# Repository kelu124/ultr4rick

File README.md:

# ultr4rick

Ultr4rick is an open ultrasound pulse-echo board, the higher-power successor to
[pic0rick](https://github.com/kelu124/pic0rick). It is built around an **RP2350B** and has:

- a 10-bit, 60 MS/s ADC (AD9215) behind an AD8331 variable-gain front end, with gain set by an MCP4812 DAC;
- a bipolar HV pulser driven by two logic lines (A = negative, B = positive, A+B = damping), fed by a SEPIC HV supply;
- a MAX14866 16-channel HV mux;
- a uSD slot, an LP5562 RGB LED driver on I2C, and USB.

The firmware can compute the Hilbert envelope (and A-law compression) of each 4096-sample capture on the board.

## The board

<table>
  <tr>
    <td width="50%"></td>
    <td width="50%"></td>
  </tr>
  <tr>
    <td><b>Front.</b> HV supply, pulser, RP2350B and receive front end (AFE). <code>PULSER_OUT</code> and
      <code>AFE_IN</code> SMA connectors on the right edge, USB-C and uSD on the left.</td>
    <td><b>Back.</b> The MAX14866 HV mux and the 8 U.FL element connectors (U18–U21, U26–U29).</td>
  </tr>
  <tr>
    <td colspan="2"></td>
  </tr>
  <tr>
    <td colspan="2"><b>Running.</b> Powered over USB-C (about 0.96 W on the inline meter), with one transducer on
      <code>PULSER_OUT</code> and <code>AFE_IN</code> through an SMA tee.</td>
  </tr>
</table>

The KiCad renders are in [`hardware/Ultr4rick_F.png`](hardware/Ultr4rick_F.png) and
[`hardware/Ultr4rick_B.png`](hardware/Ultr4rick_B.png). The photos are described in
[`docs/images/README.md`](docs/images/README.md).

## Acquisition examples

Pulse-echo on the mux: each element in turn on TX and RX with `set_one_mux(k)`, raw ADC trace (top) and on-board
Hilbert envelope (bottom). Elements 2 and 4 show echo trains: about every 13 µs on element 2 and every 20 µs on element 4. From
`python/example_dsp.ipynb`, section 13.

Idle vs. pulsed capture at gain 50, pulse 96/6000/96 ns: the excitation at 0.9 µs, the receiver recovering until
about 6 µs, and the envelope computed on the board. From `python/example_dsp.ipynb`, section 15.

## Repository layout

| Path | Contents |
|---|---|
| `docs/` | Documentation: [start here](docs/README.md) (introduction, setup and first acquisitions, firmware, Python library, repository map) |
| `hardware/` | KiCad project of the v2 board: schematic sheets per subsystem, PCB, gerbers, renders |
| `firmware/` | Pico SDK C firmware for the RP2350B. Pin map in [`firmware/PINMAP.md`](firmware/PINMAP.md), history in [`firmware/CHANGELOG.md`](firmware/CHANGELOG.md) |
| `python/` | `ultr4rick` host library, example script and notebooks. See [`python/Readme.md`](python/Readme.md) |
| `requirements.txt` | Python dependencies for `python/` |
| `TODO.md` | Hardware changes planned for the next revision |
| `LICENSE.md`, `LICENSES/` | Licenses per part of the repository |

## Quick start

Build the firmware (Pico SDK 2.3.0, `arm-none-eabi-gcc`, CMake + Ninja):

```bash
cd firmware
export PICO_SDK_PATH=$HOME/.pico-sdk/sdk/2.3.0
./build.sh -DPICO_TOOLCHAIN_PATH=/usr
# dist/ultr4rick-v<ver>-ultr4rick.uf2      stdio text REPL
# dist/ultr4rick-v<ver>-ultr4rick-dsp.uf2  on-board DSP + binary frames
```

Flashing:

1. Get the board into BOOTSEL. Either send `reboot-dfu` over the serial port, or hold BOOTSEL while plugging it in.
2. Copy the UF2 onto the `RP2350` drive that appears.

Drive it from Python:

```bash
python3 -m venv .venv && .venv/bin/pip install -r requirements.txt
cd python && ../.venv/bin/python example_dsp.py      # status, DSP self-test, captures
../.venv/bin/jupyter lab                            # example_dsp.ipynb, example_acquisition.ipynb, ...
```

```python
from ultr4rick.device import Ultr4rick
from ultr4rick import dsp
probe = Ultr4rick()                  # finds the board by USB ID
print(probe.status()["raw"])
print(dsp.check_selftest(probe.selftest()))
frame = probe.read_fft()             # 4096-sample Hilbert envelope
```

> **Safety:** the pulser generates high voltage. The firmware boots with it disarmed. Only arm it
> (`pulser arm` / `Ultr4rick.arm_pulser()`) with a transducer connected, and disarm it afterwards.

## License

- Hardware (`hardware/`): [TAPR Open Hardware License v1.0](LICENSES/TAPR-OHL-1.0.txt)
- Firmware (`firmware/`) and Python (`python/`): [GPL-3.0-or-later](LICENSES/GPL-3.0-or-later.txt)
- Documentation (`docs/` and the Markdown files): [CC BY-SA 4.0](LICENSES/CC-BY-SA-4.0.txt)

See [`LICENSE.md`](LICENSE.md) for the details and the third-party code.

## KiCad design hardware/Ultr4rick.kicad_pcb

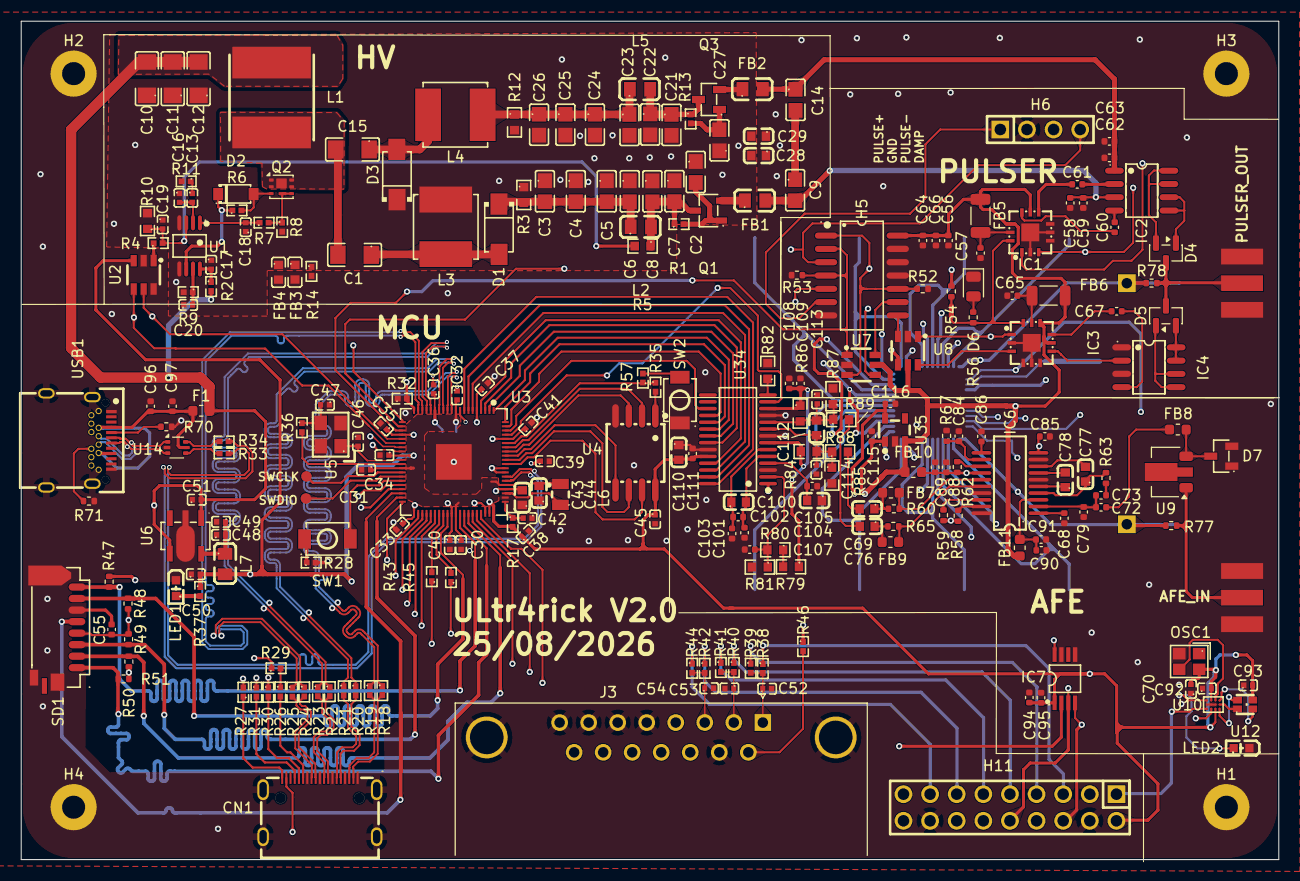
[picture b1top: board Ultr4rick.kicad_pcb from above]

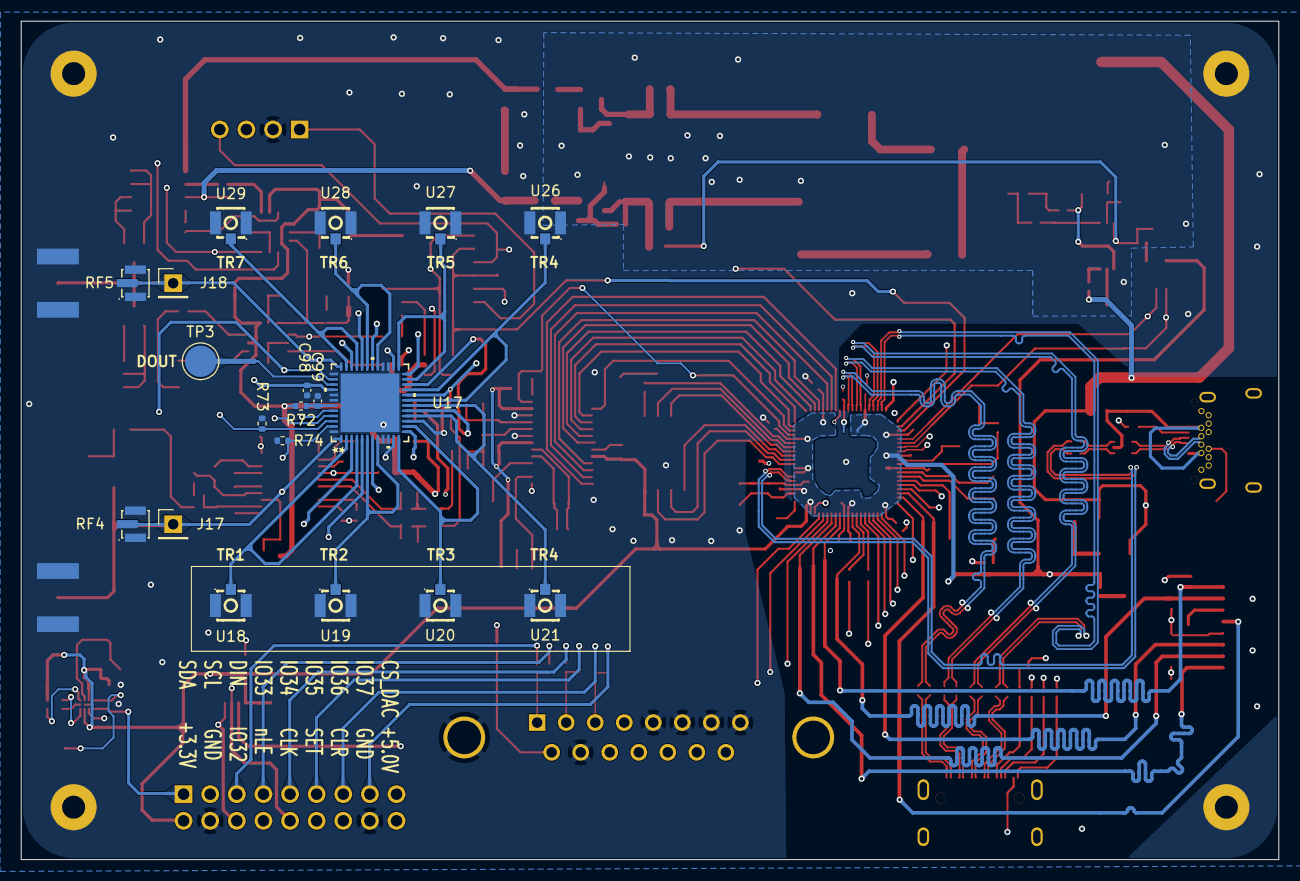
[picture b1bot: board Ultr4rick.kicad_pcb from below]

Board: 4 copper layers, 120.0 x 80.0 mm, 269 parts (19 on the bottom side), 198 nets.

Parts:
C1, C15: 2.2uF; C1206
C2, C3, C4, C5, C6, C7, C8, C21, C22, C23, C24, C25, C26, C27: 2.2uF; C0805
C9, C14: 100nF; C0805
C10, C11: 47uF; C1206
C12: 100nF; C1206
C13, C16, C30, C31, C33, C34, C35, C36, C37, C38, C39, C40, C41, C45, C49: 100nF; C0402
C17, C32, C42, C48: 4.7uF; C0402
C18: 2200pF; C0402
C19, C20: 100pF; C0402
C28, C29: 100nF; C0603
C43, C44: 4.7uF; C0603
C46, C47: 15pF; C0402
C50, C51: 10uF; C0402
C52, C53, C54: 220nF; C0402
C55, C94: 10uF; C_0402_1005Metric
C56, C57, C59, C63, C64, C65, C66, C68, C84, C86, C89, C91, C95, C99, C101, C102, C103, C105, C107, C109, C111: 100nF; C_0402_1005Metric
C58, C62, C98: 1uF; C_0402_1005Metric
C60, C61, C67, C72: 10nF; C_0402_1005Metric
C69, C76, C77, C78: 10nF; C0603
C70: 10nF; C0402
C73: 18nF; C_0402_1005Metric
C79: 22pF; C_0402_1005Metric
C85, C88, C90: 1nF; C_0402_1005Metric
C92, C93: 4u7; C0402
C96, C97: 4u7; C_0402_1005Metric
C100, C104, C110: 10uF; C0603
C108, C115, C116: 4.7uF; C_0402_1005Metric
C112: 100pF; C0603
C113, C114: 22pF; C0402
CN1: A71-05H4-111N1; HDMI-SMD_A71-05H4-111N1
D1, D3: SS320_C18199172; SMA_L4.3-W2.6-LS5.0-RD
D2: 1N4148W T4; SOD-123_L2.8-W1.8-LS3.7-RD
D4, D5: BAV99; SOT-23
D6: Green LED; D_0805_2012Metric
D7: BAV99-7-F; SOT-23-3_L2.9-W1.3-P1.90-LS2.4-BR
F1: 1A; Fuse_0603_1608Metric
FB1, FB2: 1.2Ω; L0805
FB3, FB4: 8.5Ω; L0603
FB5, FB6: 120Ohm 3 A; L_1206_3216Metric
FB7, FB8, FB9, FB10, FB11: L_0603_1608Metric
H1, H2, H3, H4: MountingHole_Pad; MountingHole_2.2mm_M2_Pad
H5: TC74VHC08F_EL,K,F_; SOP-14_L10.2-W5.3-P1.27-LS7.8-BL
H6: Header-Male-2.54_1x4; HDR-TH_4P-P2.54-V-M
H11: HX PZ2.54-2X9P ZZ; HDR-TH_18P-P2.54-V-M-R2-C9-S2.54-1
IC1, IC3: MD1213K6-G; QFN-12_L4.0-W4.0-P0.80-BL-EP1.7
IC2, IC4: TC6320TG-G; SOIC-8_L4.9-W3.9-P1.27-LS6.0-BL
IC6: AD8331ARQZ; QSOP-20_L8.7-W3.9-P0.64-LS6.0-BL
IC7: MCP4812-E_MS; MSOP-8_L3.0-W3.0-P0.65-LS4.9-BL
J1, J2: SMA_Edge; SMA_Edge_8mm
J3: DE15_Socket_HighDensity_MountingHoles; DSUB-15_Socket_Horizontal_P2.77x2.84mm_EdgePinOffset9.90mm_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
J17, J18: Conn_01x01_Pin; PinHeader_1x01_P2.54mm_Vertical
L1: 100uH; IND-SMD_L8.0-W8.0
L2, L5: 10uH; L0805
L3, L4: 1mH; IND-SMD_L6.0-W6.0_SWPA6045S
L6: 3.3uH; IND-SMD_L2.0-W1.6_AOTA-B201610S3R3-101-T
L7: MH2029-601Y; L0805
LED1, LED2: KT-0603R; LED-SMD_L1.6-W0.8-R-RD
NT1: NetTie_2; NetTie-2_SMD_Pad0.5mm
OSC1: SX2M32.768KM20F30TNN; OSC-SMD_4P-L2.5-W2.0-BL
Q1: FMMT495TA; SOT-23-3_L2.9-W1.6-P1.90-LS2.8-BR
Q2: CSD19538Q2; Texas_DQK
Q3: FMMT596TA; SOT-23-3_L2.9-W1.3-P1.90-LS2.4-BR
R1, R13: 10k; R0402
R2, R33, R34: 22Ω; R0402
R3, R12: 100k; R0603
R4: 56k; R0402
R5: 330k; R0603
R6: 1Ω; R0402
R7, R43, R45, R46: 100Ω; R0402
R8: 0.1Ω; R0402
R9: 40.2k; R0402
R10: 5.1k; R0603
R11: 4.7k; R0402
R14, R35: 0Ω; R0402
R17: 33Ω; R0402
R18, R19, R20, R21, R22, R23, R24, R25, R26: 200Ω; R0402
R27: 1.8kΩ; R0402
R28, R36, R57: 1kΩ; R0402
R29, R30, R31: 2.2kΩ; R0402
R32: 3.3kΩ; R0402
R37: 330Ω; R0402
R38, R40, R42: 510Ω; R0402
R39, R41, R44: 1KΩ; R0402
R47, R48, R49, R50, R51, R52, R53, R54, R58, R59, R62, R73, R74: 10K; R_0402_1005Metric
R56: 1K; R_0402_1005Metric
R60, R65: 100R; R_0402_1005Metric
R63: 280R; R_0402_1005Metric
R67: 12K; R_0402_1005Metric
R70, R71: 5K1; R_0402_1005Metric
R72: 10R; R_0402_1005Metric
R77, R78: 0Ω; R_0402_1005Metric
R79, R80, R81, R82, R84, R85, R86, R87: 1k; R0603
R88, R89: 18R; R0603
RF4, RF5: CONUFL001-SMD-T; IPEX-SMD_3P-L2.6-W2.6-LS3.0
SD1: TF-027-H300; TF-SMD_HYCW104-TF08-375B
SW1, SW2: TS-1088-AR02016; SW-SMD_L3.9-W3.0-P4.45
TP1, TP2: 1.0mm; TestPoint-1.0mm
TP3: TestPoint; TestPoint_Pad_D3.0mm
U1: LM3488MMX/NOPB; VSSOP-8_L3.0-W3.0-P0.65-LS4.9-BL
U2: MCP4725A1T-E/CH; SOT-23-6_L2.9-W1.6-P0.95-LS2.8-BR
U3: RP2350B; QFN-80_L10.0-W10.0-P0.40-TL-EP3.4
U4: W25Q128JVSIM; SOIC-8_L5.2-W5.2-P1.27-LS7.9-BL
U5: 12MHz; OSC-SMD_4P-L3.2-W2.5-BL_SIT8008BI
U6: XC6220B331PR-G; SOT-89-5_L4.5-W2.5-P1.50-LS4.4-BR
U7, U8: SN74LVC2G04DBVT; SOT-23-6_L2.9-W1.6-P0.95-LS2.8-BR
U9: MD0100N8-G; SOT-89-3
U10: LP5562TMX/NOPB; DSBGA-12_L1.7-W1.3-R3-C4-P0.40-TL
U12: A-SP1943B1GHR6C-C01-2T; LED-SMD_4P-L1.6-W1.5-BL_A-SP1943B1GHR6C-C01-2T
U14: USBLC6-2P6; SOT-666
U17: MAX14866UTM+T; 21-0144H_T4877-6_MXM
U18, U19, U20, U21, U26, U27, U28, U29: BWU.FL-IPEX1; IPEX-SMD_BWIPX-1-001E
U34: AD9215BRUZRL7-65; TSSOP-28_L9.7-W4.4-P0.65-LS6.4-BL
U35: XC6210B302MR; SOT-23-5_L2.9-W1.6-P0.95-LS2.8-BR
USB1: TYPEC-503DSL-ACP24; USB-C-SMD_TYPEC-324-BCP24

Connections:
5VLNA: C90.1, C91.1, FB11.2, IC6.3 (VPSL)
5VVGA: C88.1, C89.1, FB10.1, IC6.14 (VPOS), R58.1, R59.1, R62.1
+1.1V: C30.1, C31.1, C32.2, C44.2, L6.2, U3.10 (DVDD), U3.32 (DVDD), U3.51 (DVDD), U3.65 (VREG_FB)
+3.3V: C33.1, C34.1, C35.1, C36.1, C37.1, C38.1, C39.1, C40.1, C41.1, C43.2, C45.1, C50.2, C55.2, C70.2, C92.2, C93.2, C94.1, C95.1, C98.2, C110.2, C111.1, H11.2, IC7.1 (VDD), L7.2, OSC1.4 (VDD), R17.2, R37.1, R47.1, R48.1, R49.1, R50.1, R51.1, R54.1, SD1.4 (VDD), U2.3 (VDD), U3.5 (IOVDD), U3.15 (IOVDD), U3.24 (IOVDD), U3.29 (IOVDD), U3.41 (IOVDD), U3.50 (IOVDD), U3.59 (ADC_AVDD), U3.60 (IOVDD), U3.64 (VREG_VIN), U3.68 (USB_OTP_VDD), U3.69 (QSPI_IOVDD), U3.76 (IOVDD), U4.8 (VCC), U10.A2 (VDD), U10.C3 (EN/VCC), U12.3, U17.40 (VDD), U34.24 (DRVDD)
+5V: C10.2, C11.2, C12.2, C51.2, C56.1, C64.1, C66.1, C115.1, CN1.18 (+5V), F1.2, FB5.1, FB6.1, FB10.2, FB11.1, H5.14 (VCC), H11.18, IC1.8 (VH), IC1.10 (VDD2), IC3.8 (VH), IC3.10 (VDD2), L1.1 (+), R2.2, R46.1, R72.2, U6.1 (CE), U6.4 (VIN), U7.5 (VCC), U8.5 (VCC), U35.1 (VIN), U35.3 (CE)
+HV: C9.2, C58.2, C59.2, FB1.2, IC2.3 (SP)
-HV: C14.1, C62.2, C63.2, FB2.2, IC2.1 (SN)
/DAC+AFE/ECHO_IN: J2.1 (In), R77.2, U9.1 (A)
/MUX/DOUT: TP3.1 (1_1), U17.39 (DOUT)
/MUX/MUX_IN: J17.1 (Pin_1_1), R77.1, RF4.1, U17.1 (COM0), U17.5 (COM2), U17.11 (COM4), U17.15 (COM6), U17.20 (COM8), U17.24 (COM10), U17.30 (COM12), U17.34 (COM14)
/MUX/MUX_OUT: J18.1 (Pin_1_1), R78.1, RF5.1, U17.3 (COM1), U17.7 (COM3), U17.13 (COM5), U17.17 (COM7), U17.22 (COM9), U17.26 (COM11), U17.32 (COM13), U17.36 (COM15)
/MUX/NO0: U17.2 (NO0), U17.4 (NO1), U18.1
/MUX/NO2: U17.6 (NO2), U17.8 (NO3), U19.1
/MUX/NO4: U17.12 (NO4), U17.14 (NO5), U20.1
/MUX/NO6: U17.16 (NO6), U17.18 (NO7), U21.1
/MUX/NO8: U17.19 (NO8), U17.21 (NO9), U26.1
/MUX/NO10: U17.23 (NO10), U17.25 (NO11), U27.1
/MUX/NO12: U17.29 (NO12), U17.31 (NO13), U28.1
/MUX/NO14: U17.33 (NO14), U17.35 (NO15), U29.1
/MUX/TX: D4.3 (K), D5.3 (K), J1.1 (In), R78.2
/RP2350B/BLUE: C54.1, J3.3, R42.2, R44.2
/RP2350B/BOOT: SW1.1, U3.35 (RUN)
/RP2350B/GREEN: C53.1, J3.2, R40.2, R41.2
/RP2350B/HDMI_CLK_N: CN1.12 (TMDS_CLOCK-), R25.2
/RP2350B/HDMI_CLK_P: CN1.11 (TMDS_CLOCK+), R24.2
/RP2350B/HDMI_D0_N: CN1.9 (TMDS_DATA0-), R23.2
/RP2350B/HDMI_D0_P: CN1.8 (TMDS_DATA0+), R22.2
/RP2350B/HDMI_D1_N: CN1.6 (TMDS_DATA1-), R21.2
/RP2350B/HDMI_D1_P: CN1.5 (TMDS_DATA1+), R20.2
/RP2350B/HDMI_D2_N: CN1.3 (TMDS_DATA2-), R19.2
/RP2350B/HDMI_D2_P: CN1.2 (TMDS_DATA2+), R18.2
/RP2350B/RED: C52.1, J3.1, R38.2, R39.2
/RP2350B/SWCLK: TP1.1 (1_1), U3.33 (SWCLK)
/RP2350B/SWDIO: TP2.1 (1_1), U3.34 (SWDIO)
/RP2350B/USB_DN: R33.1, U3.66 (USB_DM)
/RP2350B/USB_DP: R34.1, U3.67 (USB_DP)
/SEPIC_HV/Vfb: C19.2, R4.2, R5.2, R10.1, U1.3 (FB)
/USB3/USB_DDN: R33.2, U14.4 (IO2)
/USB3/USB_DDP: R34.2, U14.6 (IO1)
/USB3/VBUS: C96.2, C97.1, F1.1, U14.5 (VBUS), USB1.A4 (VBUS), USB1.A9 (VBUS), USB1.B4 (VBUS), USB1.B9 (VBUS)
ADC_0: U3.78 (GPIO1), U34.17 (D0(LSB))
ADC_1: U3.79 (GPIO2), U34.18 (D1)
ADC_2: U3.80 (GPIO3), U34.19 (D2)
ADC_3: U3.1 (GPIO4), U34.20 (D3)
ADC_4: U3.2 (GPIO5), U34.21 (D4)
ADC_5: U3.3 (GPIO6), U34.22 (D5)
ADC_6: U3.4 (GPIO7), U34.25 (D6)
ADC_7: U3.6 (GPIO8), U34.26 (D7)
ADC_8: U3.7 (GPIO9), U34.27 (D8)
ADC_9: U3.8 (GPIO10), U34.28 (D9(MSB))
ADC_CLK: U3.77 (GPIO0), U34.13 (CLK)
AVDD: C108.1, C109.1, C116.1, R79.1, R84.1, R86.1, U34.7 (AVDD), U34.12 (AVDD), U35.5 (OUT)
AVSS: C9.1, C14.2
B: U10.A4 (B), U12.4
CLK: H11.10, IC7.3 (SCK), U3.27 (GPIO26), U17.45 (CLK)
CLK_N: R25.1, U3.19 (GPIO19)
CLK_P: R24.1, U3.18 (GPIO18)
CLR: H11.14, R74.1, U3.37 (GPIO29), U17.47 (CLR)
CS_DAC: H11.17, IC7.2 (~CS), U3.9 (GPIO11)
DAC_G: C85.1, IC6.10 (GAIN), IC7.8 (VOUTA)
DAMP: H5.3 (1Y), H6.4, IC3.1 (INA), U8.1 (1A)
DIN: H11.6, IC7.4 (SDI), U3.28 (GPIO27), U17.44 (DIN)
DVI_CEC: R29.1, U3.57 (GPIO46_ADC6)
DVI_D0_N: R23.1, U3.17 (GPIO17)
DVI_D0_P: R22.1, U3.16 (GPIO16)
DVI_D1_N: R21.1, U3.14 (GPIO15)
DVI_D1_P: R20.1, U3.13 (GPIO14)
DVI_D2_N: R19.1, U3.12 (GPIO13)
DVI_D2_P: R18.1, U3.11 (GPIO12)
DVI_SCL: R30.1, U3.56 (GPIO45_ADC5)
DVI_SDA: R31.1, U3.55 (GPIO44_ADC4)
G: U10.B4 (G), U12.1
GND: C28.1, C29.1, C30.2, C31.2, C32.1, C33.2, C34.2, C35.2, C36.2, C37.2, C38.2, C39.2, C40.2, C41.2, C42.1, C43.1, C44.1, C45.2, C46.1, C47.1, C48.1, C49.2, C50.1, C51.1, C52.2, C53.2, C54.2, C55.1, C56.2, C57.1, C58.1, C59.1, C62.1, C63.1, C64.2, C65.1, C66.2, C68.1, C70.1, C79.2, C84.2, C85.2, C86.2, C88.2, C89.2, C90.2, C91.2, C92.1, C93.1, C94.2, C95.2, C96.1, C97.2, C98.1, C99.1, C101.1, C103.1, C104.1, C105.2, C107.2, C108.2, C109.2, C110.1, C111.2, C113.1, C114.2, C115.2, C116.2, CN1.1 (TMDS_DATA2_SHIELD), CN1.4 (TMDS_DATA1_SHIELD), CN1.7 (TMDS_DATA0_SHIELD), CN1.10 (TMDS_CLOCK_SHIELD), CN1.13 (DDC/CEC_GND), CN1.20 (SHELL), CN1.21 (SHELL), CN1.22 (SHELL), CN1.23 (SHELL), D6.1, D7.1, D7.2, FB3.2, FB4.2, H1.1 (1_1), H2.1 (1_1), H3.1 (1_1), H4.1 (1_1), H5.7 (GND), H5.11 (4Y), H5.12 (4A), H5.13 (4B), H6.2, H11.4, H11.16, IC1.2 (VL), IC1.4 (GND_1), IC1.5 (VSS1), IC1.6 (VSS2), IC1.13 (GND_2), IC3.2 (VL), IC3.4 (GND_1), IC3.5 (VSS1), IC3.6 (VSS2), IC3.13 (GND_2), IC4.1 (SN), IC4.3 (SP), IC6.6 (COML), IC6.9 (MODE), IC6.17 (COMM_1), IC6.20 (COMM_2), IC7.5 (~LDAC), IC7.7 (VSS), J1.2 (Ext), J2.2 (Ext), J3.5, J3.6, J3.7, J3.8, J3.10, J3.SH, LED1.2 (K), LED2.2 (K), OSC1.2 (GND), R14.2, R28.2, R32.1, R52.2, R53.2, R67.2, R70.1, R71.2, R73.2, R74.2, R81.2, R82.2, R85.2, R87.2, RF4.2, RF4.3, RF5.2, RF5.3, SD1.6 (VSS), SD1.10, SD1.11, SW2.2, U2.2 (VSS), U2.6 (A0), U3.62 (VREG_PGND), U3.81 (GND), U4.4 (GND), U5.2 (GND), U5.4 (GND), U6.2 (VSS), U7.2 (GND), U8.2 (GND), U10.B1 (ADDR_SEL1), U10.B2 (ADDR_SEL0), U10.B3 (GND), U14.2 (GND), U17.9 (GND), U17.10 (GND), U17.27 (GND), U17.28 (GND), U17.37 (GND), U17.41 (GND), U17.42 (GND), U17.48 (GND), U17.49 (EPAD), U18.2, U18.3, U19.2, U19.3, U20.2, U20.3, U21.2, U21.3, U26.2, U26.3, U27.2, U27.3, U28.2, U28.3, U29.2, U29.3, U34.3 (SENSE), U34.8 (AGND), U34.11 (AGND), U34.23 (DRGND), U35.2 (GND), USB1.1 (EH), USB1.2 (EH), USB1.3 (EH), USB1.4 (EH), USB1.A1 (GND), USB1.A12 (GND), USB1.B1 (GND), USB1.B12 (GND)
GPIO20: R27.2, R32.2, U3.20 (GPIO20)
GPIO32: H11.5, R38.1, U3.40 (GPIO32)
GPIO33: H11.7, R39.1, U3.42 (GPIO33)
GPIO34: H11.9, R40.1, U3.43 (GPIO34)
GPIO35: H11.11, R41.1, U3.44 (GPIO35)
GPIO36: H11.13, R42.1, U3.45 (GPIO36)
GPIO37: H11.15, R44.1, U3.46 (GPIO37)
GPIO38: R43.2, U3.47 (GPIO38)
GPIO39: R45.2, U3.48 (GPIO39)
HVGND: C2.1, C3.1, C4.1, C5.1, C6.1, C7.1, C8.1, C10.1, C11.1, C12.1, C16.1, C17.1, C18.1, C19.1, C20.1, C21.2, C22.2, C23.2, C24.2, C25.2, C26.2, C27.1, C28.2, C29.2, D3.1 (K), FB3.1, FB4.1, L3.1 (+), R3.1, R8.2, R9.2, R10.2, R11.2, R12.2, R14.1, U1.4 (AGND), U1.5 (PGND)
I2C0_SCL: H11.3, U2.4 (SDA), U3.26 (GPIO25), U10.C2 (SCL)
I2C0_SDA: H11.1, U2.5 (SCL), U3.25 (GPIO24), U10.C1 (SDA)
INPUT_A: H5.1 (1A), H5.10 (3B), R52.1, U3.22 (GPIO22), U7.3 (2A)
INPUT_B: H5.2 (1B), H5.4 (2A), R53.1, U3.23 (GPIO23), U7.1 (1A)
unnamed: C13.1, R11.1
unnamed: C47.2, R36.1, U5.3
unnamed: C69.1, FB7.2, R60.2
unnamed: C72.1, FB8.2
unnamed: C73.2, R63.1
unnamed: C76.1, FB9.2, R65.2
unnamed: CN1.14 (CEC), R26.2
unnamed: CN1.19 (HP_DETECT), R27.1
unnamed: CN1.15 (SCL), R30.2
unnamed: CN1.16 (SDA), R31.2
unnamed: C1.1, D1.2 (A), L3.2 (-)
unnamed: C3.2, C4.2, C5.2, C6.2, D1.1 (K), L2.1 (+), R3.2
unnamed: D2.2 (A), Q2.3 (G), R6.2
unnamed: D2.1 (K), R6.1, U1.6 (DR)
unnamed: C15.1, D3.2 (A), L4.2 (-)
unnamed: D4.2 (A), IC2.7 (DN_1), IC2.8 (DN_2)
unnamed: D5.2 (A), IC4.7 (DN_1), IC4.8 (DN_2)
unnamed: D6.2, R56.2
unnamed: H5.5 (2B), U7.4 (2Y)
unnamed: H5.9 (3A), U7.6 (1Y)
unnamed: H5.8 (3Y), U8.3 (2A)
unnamed: C60.1, IC1.9 (OUTA)
unnamed: C61.1, IC1.7 (OUTB)
unnamed: C57.2, FB5.2, IC1.11 (VDD1)
unnamed: D4.1 (K), IC2.5 (DP_1), IC2.6 (DP_2)
unnamed: C61.2, IC2.2 (GN)
unnamed: C60.2, IC2.4 (GP)
unnamed: C67.1, IC3.9 (OUTA)
unnamed: IC3.7 (OUTB), IC4.2 (GN)
unnamed: C65.2, FB6.2, IC3.11 (VDD1)
unnamed: D5.1 (K), IC4.5 (DP_1), IC4.6 (DP_2)
unnamed: C67.2, IC4.4 (GP)
unnamed: IC6.19 (ENBL), R58.2
unnamed: IC6.18 (ENBV), R59.2
unnamed: IC6.13 (HILO), R62.2
unnamed: C72.2, C73.1, C79.1, IC6.2 (INH)
unnamed: C68.2, IC6.1 (LMD)
unnamed: C77.1, IC6.4 (LON), R63.2
unnamed: C78.1, IC6.5 (LOP)
unnamed: C84.1, IC6.12 (RCLMP), R67.1
unnamed: C86.1, IC6.11 (VCM)
unnamed: C77.2, IC6.8 (VIN)
unnamed: C78.2, IC6.7 (VIP)
unnamed: J3.9, R46.2
unnamed: J3.13, R43.1
unnamed: J3.14, R45.1
unnamed: C1.2, C15.2, L1.2 (-), Q2.1 (D), Q2.2 (D), Q2.5 (D), Q2.6 (D), Q2.8 (D)
unnamed: C7.2, C8.2, L2.2 (-), Q1.3 (C), R1.1, R5.1
unnamed: C23.1, C24.1, C25.1, C26.1, L4.1 (+), L5.1 (+), R12.1
unnamed: C21.1, C22.1, L5.2 (-), Q3.3 (C), R13.1
unnamed: LED1.1 (A), R37.2
unnamed: LED2.1 (A), U10.A1 (W)
unnamed: OSC1.3 (OUTPUT), U10.A3 (CLK_32K)
unnamed: C2.2, Q1.1 (B), R1.2
unnamed: FB1.1, Q1.2 (E)
unnamed: Q2.4 (S), Q2.7 (S), R7.2, R8.1
unnamed: C27.2, Q3.1 (B), R13.2
unnamed: FB2.1, Q3.2 (E)
unnamed: R26.1, R29.2
unnamed: R28.1, SW1.2
unnamed: R57.2, SW2.1
unnamed: R79.2, R80.1
unnamed: C13.2, C16.2, U1.2 (COMP)
unnamed: C20.2, R9.1, U1.7 (FA)
unnamed: C18.2, R7.1, U1.1 (ISEN)
unnamed: C17.2, R2.1, U1.8 (VIN)
unnamed: C42.2, R17.1, U3.61 (VREG_AVDD)
unnamed: L6.1, U3.63 (VREG_LX)
unnamed: R35.2, U4.1 (/CS)
unnamed: C48.2, C49.1, L7.1, U6.5 (VOUT)
unnamed: D7.3, FB8.1, U9.3 (B)
unnamed: C99.2, R72.1, U17.43 (VCC)
unnamed: C107.1, R80.2, R81.1, U34.2 (MODE)
unnamed: R82.1, U34.14 (PDWN)
unnamed: C100.2, C101.2, C102.1, U34.5 (REFB)
unnamed: C100.1, C102.2, C103.2, U34.6 (REFT)
unnamed: C112.1, C114.1, R84.2, R85.1, R88.1, U34.9 (VIN+)
unnamed: C112.2, C113.2, R86.2, R87.1, R89.1, U34.10 (VIN–)
unnamed: C104.2, C105.1, U34.4 (VREF)
unnamed: R70.2, USB1.A5 (CC1)
unnamed: R71.1, USB1.B5 (CC2)
OE: IC1.12 (OE), IC3.12 (OE), NT1.2, R56.1
OE_HV: NT1.1, R54.2
OR: U3.58 (GPIO47_ADC7), U34.1 (OR)
PULSE+: H5.6 (2Y), H6.1, IC1.1 (INA)
PULSE-: H6.3, IC1.3 (INB), U8.4 (2Y)
QSPI_SCLK: U3.71 (QSPI_SCLK), U4.6 (CLK)
QSPI_SD0: U3.72 (QSPI_SD0), U4.5 (DI(IO0))
QSPI_SD1: U3.74 (QSPI_SD1), U4.2 (DO(IO1))
QSPI_SD2: U3.73 (QSPI_SD2), U4.3 (/WP(IO2))
QSPI_SD3: U3.70 (QSPI_SD3), U4.7 (/HOLDor/RESET(IO3))
QSPI_SS: R35.1, R57.1, U3.75 (QSPI_SS)
R: U10.C4 (R), U12.2
SD_CMD: R49.2, SD1.3 (CMD), U3.39 (GPIO31)
SD_D0: R48.2, SD1.7 (DAT0), U3.49 (GPIO40_ADC0)
SD_D1: R47.2, SD1.8 (DAT1), U3.52 (GPIO41_ADC1)
SD_D2: R51.2, SD1.1 (DAT2), U3.53 (GPIO42_ADC2)
SD_D3: R50.2, SD1.2 (CD/DAT3), U3.54 (GPIO43_ADC3)
SD_SCK: SD1.5 (CLK), U3.38 (GPIO30)
SET: H11.12, R73.1, U3.36 (GPIO28), U17.46 (SET)
TO_ADC_H: C69.2, R88.2
TO_ADC_L: C76.2, R89.2
UD+: U14.1 (IO1), USB1.A6 (DP1), USB1.B6 (DP2)
UD-: U14.3 (IO2), USB1.A7 (DN1), USB1.B7 (DN2)
VOH: FB7.1, IC6.15 (VOH), R60.1
VOL: FB9.1, IC6.16 (VOL), R65.1
Vadj: R4.1, U2.1 (VOUT)
XIN: C46.2, U3.30 (XIN), U5.1
XOUT: R36.2, U3.31 (XOUT)
nLE: H11.8, U3.21 (GPIO21), U17.38 (*LE)
~DAMP: IC3.3 (INB), U8.6 (1Y)

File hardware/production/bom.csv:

Designator,Footprint,Quantity,Value,LCSC Part #
"C1, C15",C1206,2,2.2uF,C170101
"C10, C11",C1206,2,47uF,C403725
"C100, C104, C110",C0603,3,10uF,C96446
"C101, C102, C103, C105, C107, C109, C111, C68, C84, C86, C89, C91, C95",0402,13,100nF,C1525 
"C108, C115, C116",0402,3,4.7uF,C318563 
C112,C0603,1,100pF,C14858
"C113, C114",C0402,2,22pF,C1555
C12,C1206,1,100nF, C1945
"C13, C16",C0402,2,100nF,C162178
"C14, C9",C0805,2,100nF,C28233
C17,C0402,1,4.7uF,C6119795
C18,C0402,1,2200pF,C710671
"C19, C20",C0402,2,100pF,C576700
"C2, C21, C22, C26, C27, C6, C7, C8",C0805,8,2.2uF, C22367838
"C23, C24, C25, C3, C4, C5",C0805,6,2.2uF,C22367838
"C28, C29",C0603,2,100nF,C77058
"C30, C31, C33, C34, C35, C36, C37, C38, C39, C40, C41, C45, C49",C0402,13,100nF,C152814
"C32, C42, C48",C0402,3,4.7uF,C5718966
"C43, C44",C0603,2,4.7uF,C5360844
"C46, C47",C0402,2,15pF,C326803
"C50, C51",C0402,2,10uF,C315248
"C52, C53, C54",C0402,3,220nF,C71693
"C55, C94",0402,2,10uF,C315248 
"C56, C57, C59, C63, C64, C65, C66",0402,7,100nF,C1525
"C58, C62",0402,2,1uF,C52923
"C60, C61, C67",0402,3,10nF,C15195
"C69, C76",C0603,2,10nF,C76599
C70,C0402,1,10nF,C15195
C72,0402,1,10nF,C1518210
C73,0402,1,18nF,C106202 
"C77, C78",C0603,2,10nF,C85973
C79,0402,1,22pF,C1864677 
"C85, C88, C90",0402,3,1nF,C77018 
"C92, C93",C0402,2,4u7,C326586
"C96, C97",0402,2,4u7,C326586
C98,0402,1,1uF,C1525  
C99,0402,1,100nF,C1525  
CN1,HDMI-SMD_A71-05H4-111N1,1,A71-05H4-111N1,C2682170
"D1, D3",SMA_L4.3-W2.6-LS5.0-RD,2,SS320_C18199172,C18199172
D2,SOD-123_L2.8-W1.8-LS3.7-RD,1,1N4148W T4,C2099
"D4, D5",SOT-23,2,BAV99,C2500
D6,0805,1,Green LED,C84260
D7,SOT-23-3_L2.9-W1.3-P1.90-LS2.4-BR,1,BAV99-7-F,C106919 
F1,0603,1,1A,C207017
"FB1, FB2",L0805,2,1.2Ω,C46435
"FB10, FB11, FB7, FB8, FB9",0603,5,~,C14709 
"FB3, FB4",L0603,2,8.5Ω,C5339211
"FB5, FB6",1206,2,120Ohm 3 A,C98293
H11,HDR-TH_18P-P2.54-V-M-R2-C9-S2.54-1,1,HX PZ2.54-2X9P ZZ,C42372517
H5,SOP-14_L10.2-W5.3-P1.27-LS7.8-BL,1,"TC74VHC08F_EL,K,F_",C6880155
H6,HDR-TH_4P-P2.54-V-M,1,Header-Male-2.54_1x4,C124378
"IC1, IC3",QFN-12_L4.0-W4.0-P0.80-BL-EP1.7,2,MD1213K6-G,C621434
"IC2, IC4",SOIC-8_L4.9-W3.9-P1.27-LS6.0-BL,2,TC6320TG-G,C624992
IC6,QSOP-20_L8.7-W3.9-P0.64-LS6.0-BL,1,AD8331ARQZ,C578697 
IC7,MSOP-8_L3.0-W3.0-P0.65-LS4.9-BL,1,MCP4812-E_MS,C219484 
"J1, J2",SMA_Edge_8mm,2,SMA_Edge,RFPC-SMA23-FN-095-A
"J17, J18",PinHeader_1x01_P2.54mm_Vertical,2,Conn_01x01_Pin,C81276 
J3,DSUB-15_Socket_Horizontal_P2.77x2.84mm_EdgePinOffset9.90mm_Housed_MountingHolesOffset11.32mm,1,DE15_Socket_HighDensity_MountingHoles,C3108041
L1,IND-SMD_L8.0-W8.0,1,100uH,C142103
"L2, L5",L0805,2,10uH,C52723027
"L3, L4",IND-SMD_L6.0-W6.0_SWPA6045S,2,1mH,C133757
L6,IND-SMD_L2.0-W1.6_AOTA-B201610S3R3-101-T,1,3.3uH,C42411119
L7,L0805,1,MH2029-601Y,C840592
"LED1, LED2",LED-SMD_L1.6-W0.8-R-RD,2,KT-0603R,C2286
OSC1,OSC-SMD_4P-L2.5-W2.0-BL,1,SX2M32.768KM20F30TNN,C2901603
Q1,SOT-23-3_L2.9-W1.6-P1.90-LS2.8-BR,1,FMMT495TA,C47296
Q2,Texas_DQK,1,CSD19538Q2,C2838636
Q3,SOT-23-3_L2.9-W1.3-P1.90-LS2.4-BR,1,FMMT596TA,C150439
"R1, R13",R0402,2,10k,C25744
R10,R0603,1,5.1k, C23186
R11,R0402,1,4.7k,C25900
"R12, R3",R0603,2,100k,C25803
R14,R0402,1,0Ω,C17168
R17,R0402,1,33Ω,C2906931
"R18, R19, R20, R21, R22, R23, R24, R25, R26",R0402,9,200Ω,C114952
R2,R0402,1,22Ω,C25092
R27,R0402,1,1.8kΩ,C163481
"R28, R36",R0402,2,1kΩ,C2906864
"R29, R30, R31",R0402,3,2.2kΩ,C2906865
R32,R0402,1,3.3kΩ,C2909345
"R33, R34",R0402,2,22Ω,C2929994
R35,R0402,1,0Ω,C2097066
R37,R0402,1,330Ω,C2906929
"R38, R40, R42",R0402,3,510Ω,C276273
"R39, R41, R44",R0402,3,1KΩ,C11702
R4,R0402,1,56k,C114756
"R43, R45, R7",R0402,3,100Ω,C25076
"R47, R48, R49, R50, R51, R58, R59, R62",0402,8,10K,C60490 
R5,R0603,1,330k,C23137
"R52, R53, R54",0402,3,10K,C25744
R56,0402,1,1K,C11702
R6,R0402,1,1Ω,C412890
"R60, R65",0402,2,100R,C106232 
R63,0402,1,280R,C2929998 
R67,0402,1,12K,C2909316 
"R70, R71",0402,2,5K1,C105873
R72,0402,1,10R,C138066
"R73, R74",0402,2,10K,C60490  
"R77, R78",0402,2,0Ω,C106231
"R79, R80, R81, R82, R84, R85, R86, R87",R0603,8,1k,C21190
R8,R0402,1,0.1Ω,C474056
"R88, R89",R0603,2,18R,C245924
R9,R0402,1,40.2k,C25893
"RF4, RF5",IPEX-SMD_3P-L2.6-W2.6-LS3.0,2,CONUFL001-SMD-T,C22418213
SD1,TF-SMD_HYCW104-TF08-375B,1,TF-027-H300,C5310495
SW1,SW-SMD_L3.9-W3.0-P4.45,1,TS-1088-AR02016,C720477
U1,VSSOP-8_L3.0-W3.0-P0.65-LS4.9-BL,1,LM3488MMX/NOPB,C80782
U10,DSBGA-12_L1.7-W1.3-R3-C4-P0.40-TL,1,LP5562TMX/NOPB,C544465
U12,LED-SMD_4P-L1.6-W1.5-BL_A-SP1943B1GHR6C-C01-2T,1,A-SP1943B1GHR6C-C01-2T,C19171342
U14,SOT-666,1,USBLC6-2P6,C15999
U17,21-0144H_T4877-6_MXM,1,MAX14866UTM+T,C2673849 
"U18, U19, U20, U21, U26, U27, U28, U29",IPEX-SMD_BWIPX-1-001E,8,BWU.FL-IPEX1,C5137195
U2,SOT-23-6_L2.9-W1.6-P0.95-LS2.8-BR,1,MCP4725A1T-E/CH,C61423
U3,QFN-80_L10.0-W10.0-P0.40-TL-EP3.4,1,RP2350B,C42415655
U34,TSSOP-28_L9.7-W4.4-P0.65-LS6.4-BL,1,AD9215BRUZRL7-65,C653268
U35,SOT-23-5_L2.9-W1.6-P0.95-LS2.8-BR,1,XC6210B302MR,C23378034
U4,SOIC-8_L5.2-W5.2-P1.27-LS7.9-BL,1,W25Q128JVSIM,C2613930
U5,OSC-SMD_4P-L3.2-W2.5-BL_SIT8008BI,1,12MHz,C20625731
U6,SOT-89-5_L4.5-W2.5-P1.50-LS4.4-BR,1,XC6220B331PR-G,C3013658
"U7, U8",SOT-23-6_L2.9-W1.6-P0.95-LS2.8-BR,2,SN74LVC2G04DBVT,C2860342
U9,SOT-89-3,1,MD0100N8-G,C629131
USB1,USB-C-SMD_TYPEC-324-BCP24,1,TYPEC-503DSL-ACP24,C2835314

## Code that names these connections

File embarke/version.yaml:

# ultr4rick (embarke) firmware version.
#
# Format: A.B.C  (major.minor.patch)
#   A (major)  0-99   -- managed by the maintainer (Luc)
#   B (minor)  0-99   -- managed by the maintainer (Luc)
#   C (patch)  0-999  -- bumped by Claude on every change to firmware/ files
#
# `changes` is a short, single-line, double-quoted summary of what changed vs
# the previous version. It is embedded in the binary (the `version` CLI command)
# and used as the GitHub release body by .github/workflows/firmware.yml.
version: "0.1.12"
changes: "embarke: identity now Ultr4rick (USB strings, U4RK frame magic). RP2350B-only board (boards/embarke.h). Pulser on GPIO22/23 A/B (00 off, A neg, B pos, AB damp), MCP4812+MAX14866 on shared SPI1 GPIO26/27 (CS_DAC 11, nLE 21, SET 28, CLR 29). RP2040/pico2 builds dropped."

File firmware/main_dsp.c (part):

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int main(void) {
    bi_decl(bi_program_description(
        "Ultr4rick RP2350B 4096-sample Hilbert envelope and A-law firmware"));
    bi_decl(bi_pin_mask_with_name(0x7ffu, "ADC clock GPIO0 and data GPIO1..10"));
    bi_decl(bi_2pins_with_names(
        U4RK_PULSER_A_PIN, "Pulser A",
        U4RK_PULSER_B_PIN, "Pulser B"));
    bi_decl(bi_2pins_with_names(
        U4RK_SPI_SCK_PIN, "SPI1 SCK (MCP4812 + MAX14866)",
        U4RK_SPI_TX_PIN, "SPI1 DIN (MCP4812 + MAX14866)"));
    bi_decl(bi_2pins_with_names(
        U4RK_DAC_CS_PIN, "MCP4812 CS_DAC",
        U4RK_MUX_LE_PIN, "MAX14866 nLE"));
    bi_decl(bi_2pins_with_names(
        U4RK_MUX_SET_PIN, "MAX14866 SET",
        U4RK_MUX_CLR_PIN, "MAX14866 CLR"));
    bi_decl(bi_2pins_with_names(
        U4RK_I2C_SDA_PIN, "I2C0 SDA (LP5562 status LED)",
        U4RK_I2C_SCL_PIN, "I2C0 SCL (LP5562 status LED)"));
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
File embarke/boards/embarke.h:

/*
 * embarke RP2350B board definition (Ultr4rick v2 hardware).
 *
 * This intentionally does not inherit boards/pico2.h: that header selects the
 * 30-GPIO RP2350A package, and this board uses GPIO40..43 (uSD) which only
 * exist on the 48-GPIO RP2350B. No radio (no CYW43). See PINMAP.md.
 */
#ifndef _BOARDS_EMBARKE_H
#define _BOARDS_EMBARKE_H

pico_board_cmake_set(PICO_PLATFORM, rp2350)

#define EMBARKE
#define PICO_RP2350A 0

/* U5: 12 MHz crystal. */
#ifndef PICO_XOSC_FREQ_HZ
#define PICO_XOSC_FREQ_HZ 12000000
#endif

/* I2C0 on GPIO24 (SDA) / GPIO25 (SCL): LP5562 LED driver, MCP4725. */
#ifndef PICO_DEFAULT_I2C
#define PICO_DEFAULT_I2C 0
#endif
#ifndef PICO_DEFAULT_I2C_SDA_PIN
#define PICO_DEFAULT_I2C_SDA_PIN 24
#endif
#ifndef PICO_DEFAULT_I2C_SCL_PIN
#define PICO_DEFAULT_I2C_SCL_PIN 25
#endif

/* SPI1 on GPIO26 (SCK) / GPIO27 (TX), shared by the MCP4812 and MAX14866. */
#ifndef PICO_DEFAULT_SPI
#define PICO_DEFAULT_SPI 1
#endif
#ifndef PICO_DEFAULT_SPI_SCK_PIN
#define PICO_DEFAULT_SPI_SCK_PIN 26
#endif
#ifndef PICO_DEFAULT_SPI_TX_PIN
#define PICO_DEFAULT_SPI_TX_PIN 27
#endif
#ifndef PICO_DEFAULT_SPI_CSN_PIN
#define PICO_DEFAULT_SPI_CSN_PIN 11
#endif

/* U4: W25Q128JV, 16 MiB external QSPI flash. */
#define PICO_BOOT_STAGE2_CHOOSE_W25Q080 1
#ifndef PICO_FLASH_SPI_CLKDIV
#define PICO_FLASH_SPI_CLKDIV 2
#endif
pico_board_cmake_set_default(PICO_FLASH_SIZE_BYTES, (16 * 1024 * 1024))
#ifndef PICO_FLASH_SIZE_BYTES
#define PICO_FLASH_SIZE_BYTES (16 * 1024 * 1024)
#endif

pico_board_cmake_set_default(PICO_RP2350_A2_SUPPORTED, 1)
#ifndef PICO_RP2350_A2_SUPPORTED
#define PICO_RP2350_A2_SUPPORTED 1
#endif

#endif

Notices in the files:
firmware/main_dsp.c:
SPDX-License-Identifier: GPL-3.0-or-later
